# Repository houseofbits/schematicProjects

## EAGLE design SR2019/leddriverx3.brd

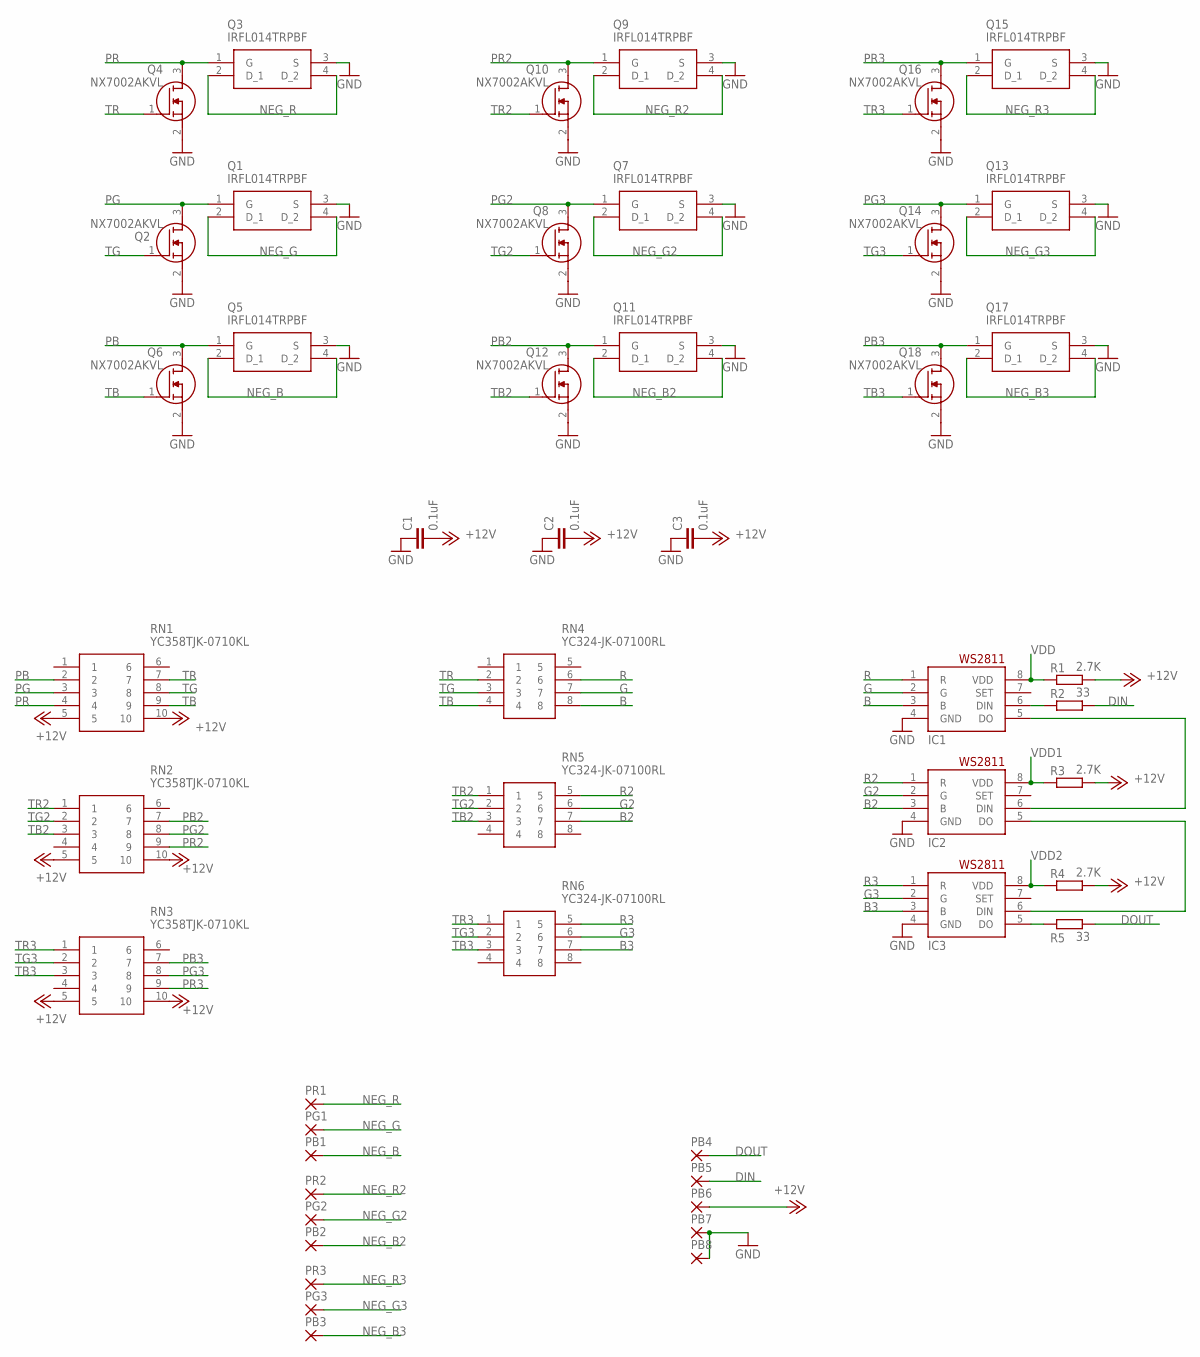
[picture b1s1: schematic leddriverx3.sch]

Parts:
C1, C2, C3: 0.1uF; C1206
IC1, IC2, IC3: WS2811-SOP8; SO08-SKINNYPADS
PB1, PB2, PB3, PB4, PB5, PB6, PB7, PB8: 3,81/1,4
PG1, PG2, PG3: 3,81/1,4
PR1, PR2, PR3: 3,81/1,4
Q1, Q3, Q5, Q7, Q9, Q11, Q13, Q15, Q17: IRFL014TRPBF; SOT230P700X180-4N
Q2, Q4, Q6, Q8, Q10, Q12, Q14, Q16, Q18: NX7002AKVL; SOT95P230X110-3N
R1, R3, R4: 2.7K; R1206
R2, R5: 33; R1206
RN1, RN2, RN3: YC358TJK-0710KL; YC358T
RN4, RN5, RN6: YC324-JK-07100RL; YC324JK07100RL

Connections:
+12V: C1.2, C2.2, C3.2, PB6.1, R1.2, R3.2, R4.2, RN1.5, RN1.10, RN2.5, RN2.10, RN3.5, RN3.10
B: IC1.3 (B), RN4.8
B2: IC2.3 (B), RN5.7
B3: IC3.3 (B), RN6.7
DIN: PB5.1, R2.2
DOUT: PB4.1, R5.2
G: IC1.2 (G), RN4.7
G2: IC2.2 (G), RN5.6
G3: IC3.2 (G), RN6.6
GND: C1.1, C2.1, C3.1, IC1.4 (GND), IC2.4 (GND), IC3.4 (GND), PB7.1, PB8.1, Q1.3 (S), Q2.2 (S), Q3.3 (S), Q4.2 (S), Q5.3 (S), Q6.2 (S), Q7.3 (S), Q8.2 (S), Q9.3 (S), Q10.2 (S), Q11.3 (S), Q12.2 (S), Q13.3 (S), Q14.2 (S), Q15.3 (S), Q16.2 (S), Q17.3 (S), Q18.2 (S)
unnamed: IC1.6 (DIN), R2.1
unnamed: IC3.5 (DO), R5.1
unnamed: IC1.5 (DO), IC2.6 (DIN)
unnamed: IC2.5 (DO), IC3.6 (DIN)
NEG_B: PB1.1, Q5.2 (D_1), Q5.4 (D_2)
NEG_B2: PB2.1, Q11.2 (D_1), Q11.4 (D_2)
NEG_B3: PB3.1, Q17.2 (D_1), Q17.4 (D_2)
NEG_G: PG1.1, Q1.2 (D_1), Q1.4 (D_2)
NEG_G2: PG2.1, Q7.2 (D_1), Q7.4 (D_2)
NEG_G3: PG3.1, Q13.2 (D_1), Q13.4 (D_2)
NEG_R: PR1.1, Q3.2 (D_1), Q3.4 (D_2)
NEG_R2: PR2.1, Q9.2 (D_1), Q9.4 (D_2)
NEG_R3: PR3.1, Q15.2 (D_1), Q15.4 (D_2)
PB: Q5.1 (G), Q6.3 (D), RN1.2
PB2: Q11.1 (G), Q12.3 (D), RN2.7
PB3: Q17.1 (G), Q18.3 (D), RN3.7
PG: Q1.1 (G), Q2.3 (D), RN1.3
PG2: Q7.1 (G), Q8.3 (D), RN2.8
PG3: Q13.1 (G), Q14.3 (D), RN3.8
PR: Q3.1 (G), Q4.3 (D), RN1.4
PR2: Q9.1 (G), Q10.3 (D), RN2.9
PR3: Q15.1 (G), Q16.3 (D), RN3.9
R: IC1.1 (R), RN4.6
R2: IC2.1 (R), RN5.5
R3: IC3.1 (R), RN6.5
TB: Q6.1 (G), RN1.9, RN4.4
TB2: Q12.1 (G), RN2.3, RN5.3
TB3: Q18.1 (G), RN3.3, RN6.3
TG: Q2.1 (G), RN1.8, RN4.3
TG2: Q8.1 (G), RN2.2, RN5.2
TG3: Q14.1 (G), RN3.2, RN6.2
TR: Q4.1 (G), RN1.7, RN4.2
TR2: Q10.1 (G), RN2.1, RN5.1
TR3: Q16.1 (G), RN3.1, RN6.1
VDD: IC1.8 (VDD), R1.1
VDD1: IC2.8 (VDD), R3.1
VDD2: IC3.8 (VDD), R4.1

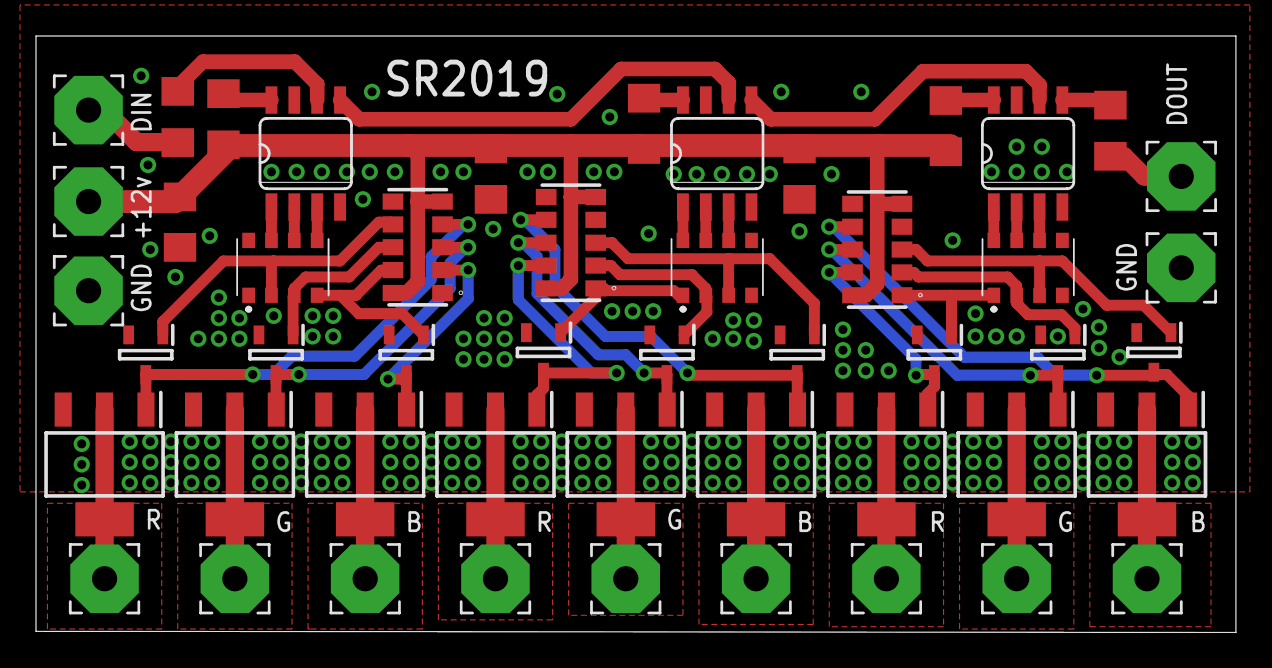
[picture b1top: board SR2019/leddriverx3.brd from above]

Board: 2 copper layers, 66.7 x 33.1 mm, 49 parts (0 on the bottom side), 47 nets.

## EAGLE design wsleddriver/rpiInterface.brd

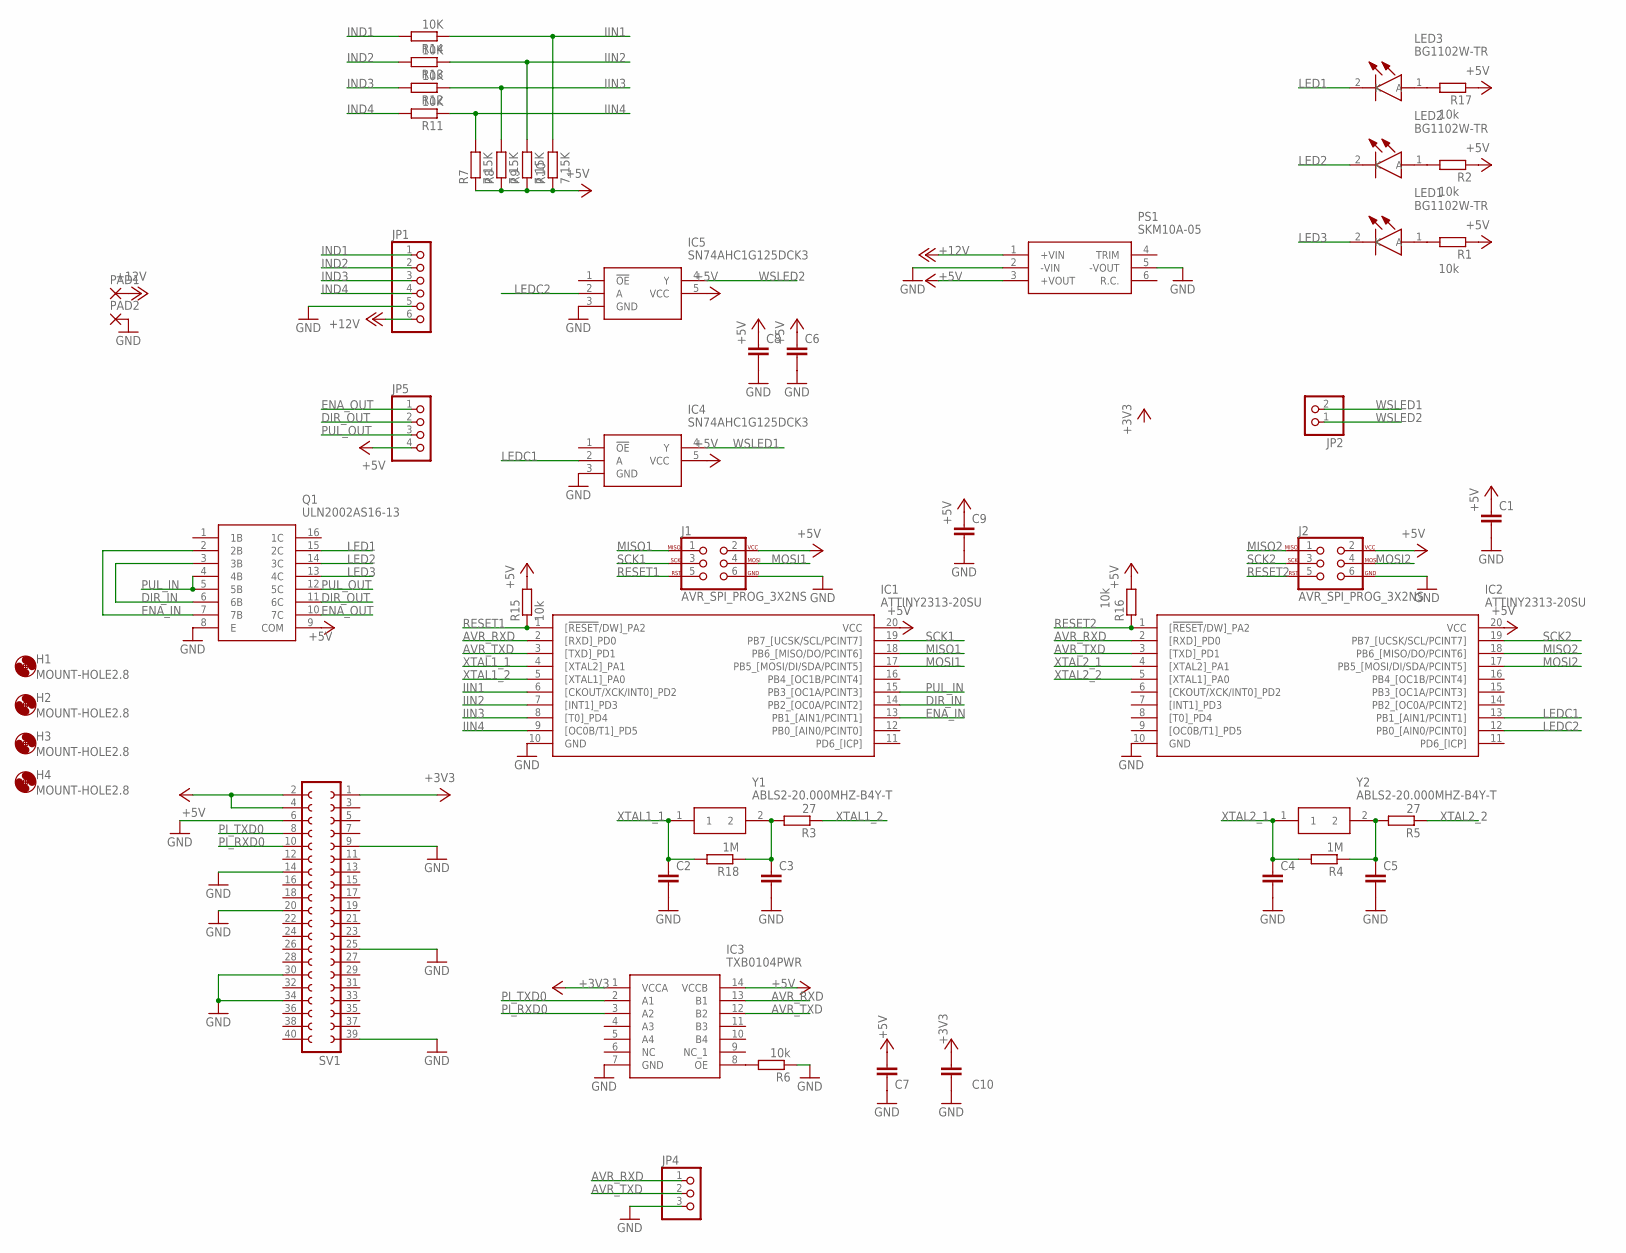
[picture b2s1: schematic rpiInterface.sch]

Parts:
C1, C2, C3, C4, C5, C6, C7, C8, C9, C10: C-EUC1206; C1206
H1, H2, H3, H4: MOUNT-HOLE2.8; 2,8
IC1, IC2: ATTINY2313-20SU; SOIC127P1032X265-20N
IC3: TXB0104PWR; SOP65P640X120-14N
IC4, IC5: SN74AHC1G125DCK3; SOT65P210X110-5N
J1, J2: AVR_SPI_PROG_3X2NS; 2X3-NS
JP1: PINHD-1X6; 1X06
JP2: PINHD-1X2; 1X02
JP4: PINHD-1X3; 1X03
JP5: PINHD-1X4; 1X04
LED1, LED2, LED3: BG1102W-TR; BG1102WTR
PAD1, PAD2: 3,17/1,3
PS1: SKM10A-05; SKM10A05
Q1: ULN2002AS16-13; SOIC127P605X126-16N
R1, R2, R6, R15, R16, R17: 10k; R1206
R3, R5: 27; R1206
R4, R18: 1M; R1206
R7, R8, R9, R10: 7.15K; R1206
R11, R12, R13, R14: 10K; R1206
SV1: FE20-2
Y1, Y2: ABLS2-20.000MHZ-B4Y-T; HC/49US-(AT49)_1

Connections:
+3V3: C10.1, IC3.1 (VCCA), SV1.1
+5V: C1.1, C6.1, C7.1, C8.1, C9.1, IC1.20 (VCC), IC2.20 (VCC), IC3.14 (VCCB), IC4.5 (VCC), IC5.5 (VCC), J1.2, J2.2, JP5.4, PS1.3 (+VOUT), Q1.9 (COM), R1.1, R2.1, R7.1, R8.1, R9.1, R10.1, R15.2, R16.2, R17.1, SV1.2, SV1.4
+12V: JP1.6, PAD1.1, PS1.1 (+VIN)
AVR_RXD: IC1.2 ([RXD]_PD0), IC2.2 ([RXD]_PD0), IC3.13 (B1), JP4.1
AVR_TXD: IC1.3 ([TXD]_PD1), IC2.3 ([TXD]_PD1), IC3.12 (B2), JP4.2
DIR_IN: IC1.14 (PB2_[OC0A/PCINT2]), Q1.3 (3B), Q1.6 (6B)
DIR_OUT: JP5.2, Q1.11 (6C)
ENA_IN: IC1.13 (PB1_[AIN1/PCINT1]), Q1.2 (2B), Q1.7 (7B)
ENA_OUT: JP5.1, Q1.10 (7C)
GND: C1.2, C2.2, C3.2, C4.2, C5.2, C6.2, C7.2, C8.2, C9.2, C10.2, IC1.10 (GND), IC2.10 (GND), IC3.7 (GND), IC4.3 (GND), IC5.3 (GND), J1.6, J2.6, JP1.5, JP4.3, PAD2.1, PS1.2 (-VIN), PS1.5 (-VOUT), Q1.8 (E), R6.1, SV1.6, SV1.9, SV1.14, SV1.20, SV1.25, SV1.30, SV1.34, SV1.39
IIN1: IC1.6 ([CKOUT/XCK/INT0]_PD2), R10.2, R14.1
IIN2: IC1.7 ([INT1]_PD3), R9.2, R13.1
IIN3: IC1.8 ([T0]_PD4), R8.2, R12.1
IIN4: IC1.9 ([OC0B/T1]_PD5), R7.2, R11.1
IND1: JP1.1, R14.2
IND2: JP1.2, R13.2
IND3: JP1.3, R12.2
IND4: JP1.4, R11.2
LED1: LED3.2 (K), Q1.15 (2C)
LED2: LED2.2 (K), Q1.14 (3C)
LED3: LED1.2 (K), Q1.13 (4C)
LEDC1: IC2.13 (PB1_[AIN1/PCINT1]), IC4.2 (A)
LEDC2: IC2.12 (PB0_[AIN0/PCINT0]), IC5.2 (A)
MISO1: IC1.18 (PB6_[MISO/DO/PCINT6]), J1.1
MISO2: IC2.18 (PB6_[MISO/DO/PCINT6]), J2.1
MOSI1: IC1.17 (PB5_[MOSI/DI/SDA/PCINT5]), J1.4
MOSI2: IC2.17 (PB5_[MOSI/DI/SDA/PCINT5]), J2.4
unnamed: C3.1, R3.2, R18.1, Y1.2
unnamed: C5.1, R4.1, R5.2, Y2.2
unnamed: LED1.1 (A), R1.2
unnamed: LED2.1 (A), R2.2
unnamed: LED3.1 (A), R17.2
unnamed: IC3.8 (OE), R6.2
PI_RXD0: IC3.3 (A2), SV1.10
PI_TXD0: IC3.2 (A1), SV1.8
PUL_IN: IC1.15 (PB3_[OC1A/PCINT3]), Q1.4 (4B), Q1.5 (5B)
PUL_OUT: JP5.3, Q1.12 (5C)
RESET1: IC1.1 ([!RESET!/DW]_PA2), J1.5, R15.1
RESET2: IC2.1 ([!RESET!/DW]_PA2), J2.5, R16.1
SCK1: IC1.19 (PB7_[UCSK/SCL/PCINT7]), J1.3
SCK2: IC2.19 (PB7_[UCSK/SCL/PCINT7]), J2.3
WSLED1: IC4.4 (Y), JP2.2
WSLED2: IC5.4 (Y), JP2.1
XTAL1_1: C2.1, IC1.4 ([XTAL2]_PA1), R18.2, Y1.1
XTAL1_2: IC1.5 ([XTAL1]_PA0), R3.1
XTAL2_1: C4.1, IC2.4 ([XTAL2]_PA1), R4.2, Y2.1
XTAL2_2: IC2.5 ([XTAL1]_PA0), R5.1

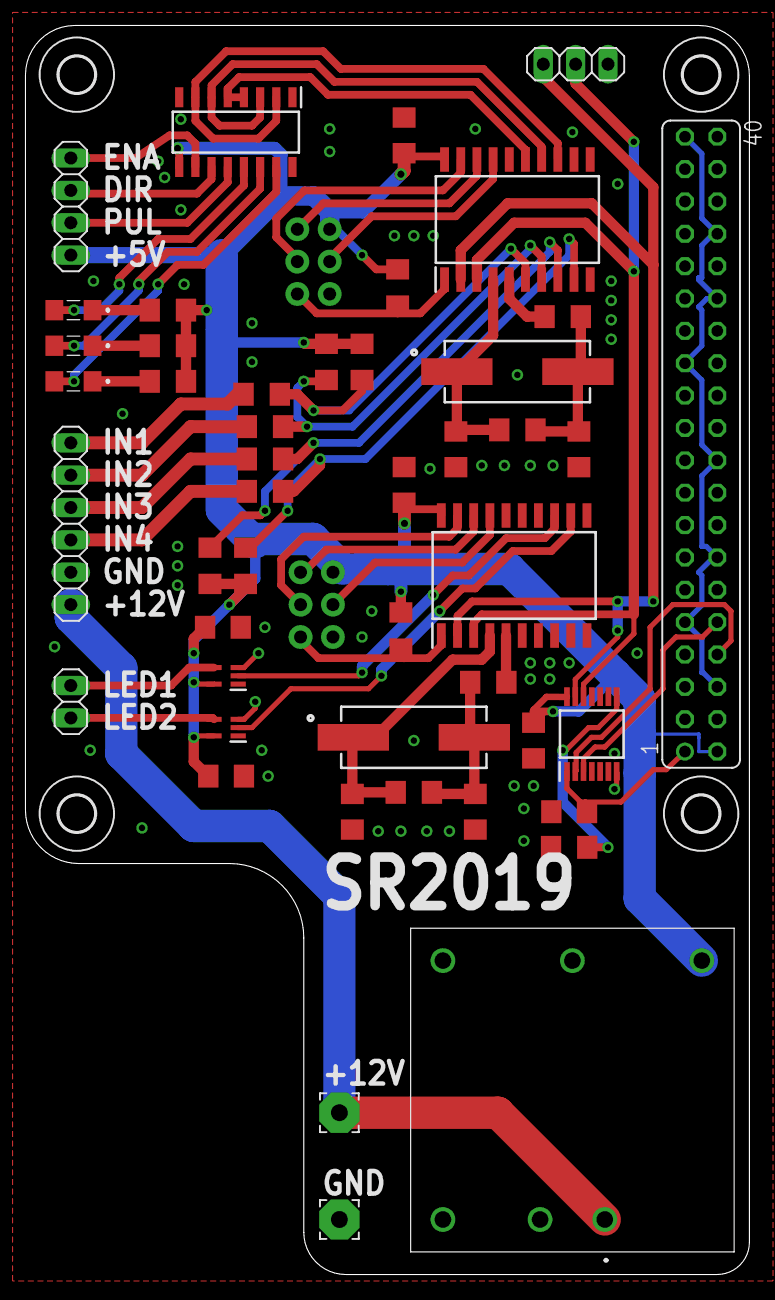
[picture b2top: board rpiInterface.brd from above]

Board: 2 copper layers, 56.8 x 98.0 mm, 53 parts (0 on the bottom side), 47 nets.

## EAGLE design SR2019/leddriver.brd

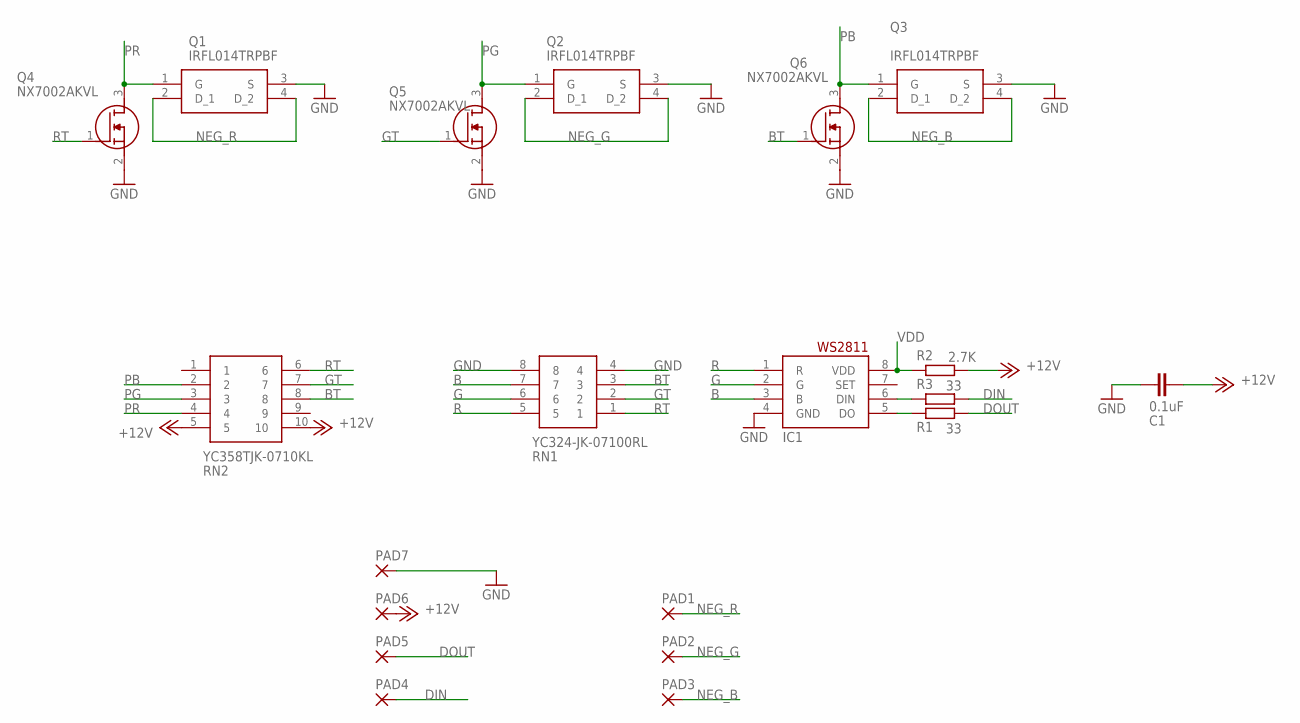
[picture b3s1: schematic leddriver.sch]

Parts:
C1: 0.1uF; C1206
IC1: WS2811-SOP8; SO08-SKINNYPADS
PAD1, PAD2, PAD3, PAD4, PAD5, PAD6, PAD7: 3,81/1,4
Q1, Q2, Q3: IRFL014TRPBF; SOT230P700X180-4N
Q4, Q5, Q6: NX7002AKVL; SOT95P230X110-3N
R1, R3: 33; R1206
R2: 2.7K; R1206
RN1: YC324-JK-07100RL; YC324JK07100RL
RN2: YC358TJK-0710KL; YC358T

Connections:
+12V: C1.2, PAD6.1, R2.1, RN2.5, RN2.10
B: IC1.3 (B), RN1.7
BT: Q6.1 (G), RN1.3, RN2.8
DIN: PAD4.1, R3.1
DOUT: PAD5.1, R1.1
G: IC1.2 (G), RN1.6
GND: C1.1, IC1.4 (GND), PAD7.1, Q1.3 (S), Q2.3 (S), Q3.3 (S), Q4.2 (S), Q5.2 (S), Q6.2 (S), RN1.4, RN1.8
GT: Q5.1 (G), RN1.2, RN2.7
unnamed: IC1.6 (DIN), R3.2
unnamed: IC1.5 (DO), R1.2
NEG_B: PAD3.1, Q3.2 (D_1), Q3.4 (D_2)
NEG_G: PAD2.1, Q2.2 (D_1), Q2.4 (D_2)
NEG_R: PAD1.1, Q1.2 (D_1), Q1.4 (D_2)
PB: Q3.1 (G), Q6.3 (D), RN2.2
PG: Q2.1 (G), Q5.3 (D), RN2.3
PR: Q1.1 (G), Q4.3 (D), RN2.4
R: IC1.1 (R), RN1.5
RT: Q4.1 (G), RN1.1, RN2.6
VDD: IC1.8 (VDD), R2.2

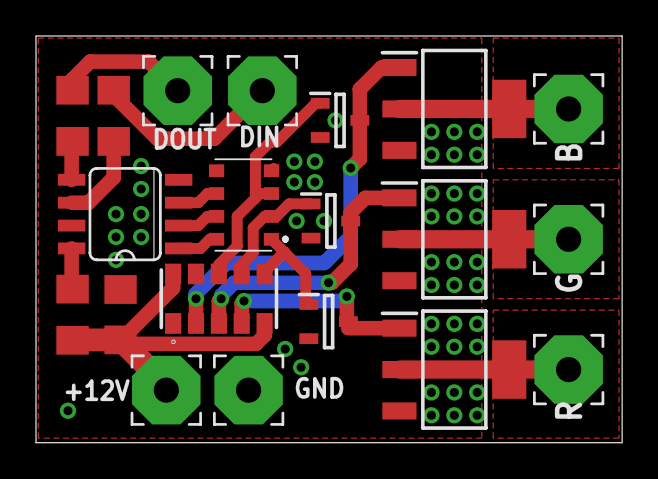
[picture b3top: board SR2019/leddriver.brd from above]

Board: 2 copper layers, 32.6 x 22.6 mm, 20 parts (0 on the bottom side), 19 nets.

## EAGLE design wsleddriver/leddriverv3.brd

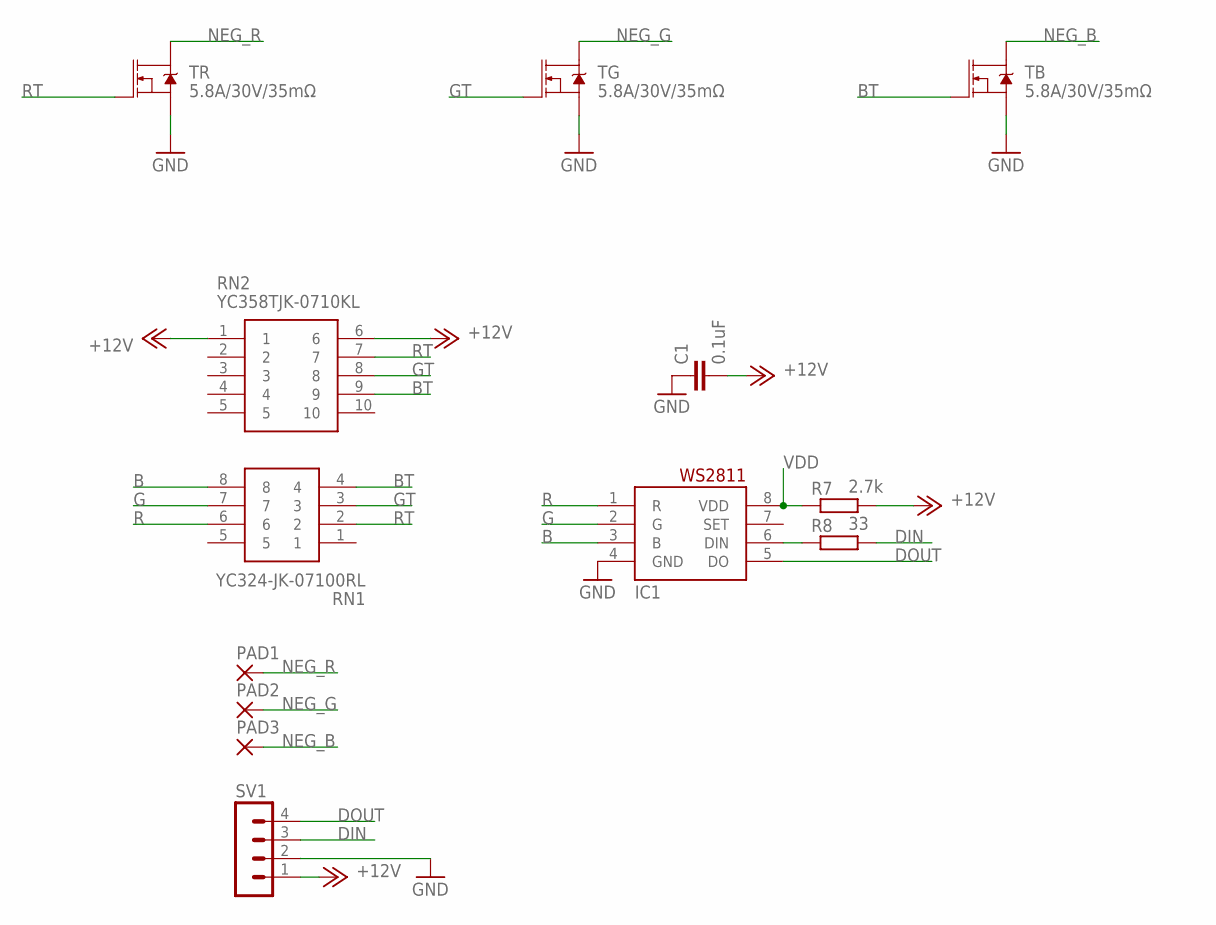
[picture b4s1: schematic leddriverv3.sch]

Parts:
C1: 0.1uF; C1206
IC1: WS2811-SOP8; SO08-SKINNYPADS
PAD1, PAD2, PAD3: 3,81/1,4
R7: 2.7k; R0805
R8: 33; R0805
RN1: YC324-JK-07100RL; YC324JK07100RL
RN2: YC358TJK-0710KL; YC358T
SV1: MA04-1
TB: 5.8A/30V/35mΩ; SOT23-3
TG: 5.8A/30V/35mΩ; SOT23-3
TR: 5.8A/30V/35mΩ; SOT23-3

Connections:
+12V: C1.2, R7.2, RN2.1, RN2.6, SV1.1
B: IC1.3 (B), RN1.8
BT: RN1.4, RN2.9, TB.1 (G)
DIN: R8.2, SV1.3
DOUT: IC1.5 (DO), SV1.4
G: IC1.2 (G), RN1.7
GND: C1.1, IC1.4 (GND), SV1.2, TB.2 (S), TG.2 (S), TR.2 (S)
GT: RN1.3, RN2.8, TG.1 (G)
unnamed: IC1.6 (DIN), R8.1
NEG_B: PAD3.1, TB.3 (D)
NEG_G: PAD2.1, TG.3 (D)
NEG_R: PAD1.1, TR.3 (D)
R: IC1.1 (R), RN1.6
RT: RN1.2, RN2.7, TR.1 (G)
VDD: IC1.8 (VDD), R7.1

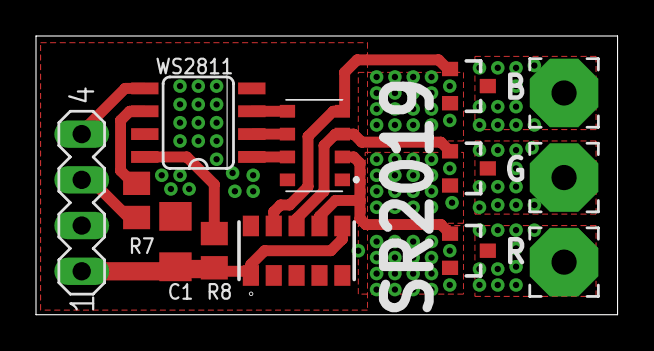
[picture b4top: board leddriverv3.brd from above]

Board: 2 copper layers, 32.3 x 15.5 mm, 13 parts (0 on the bottom side), 15 nets.

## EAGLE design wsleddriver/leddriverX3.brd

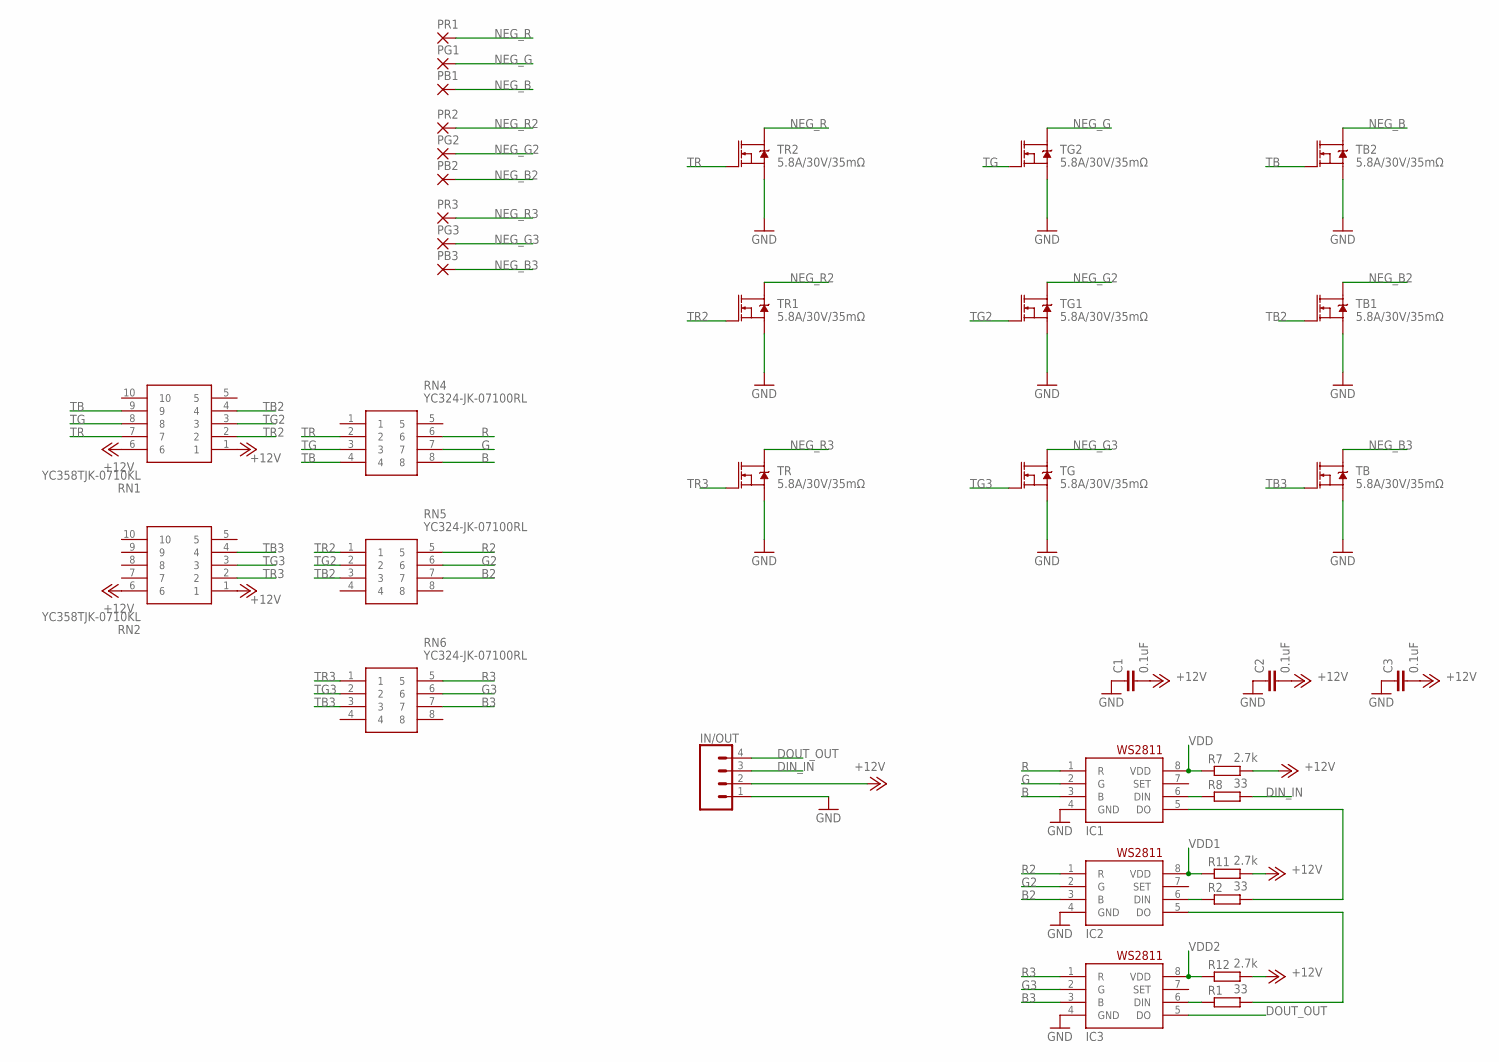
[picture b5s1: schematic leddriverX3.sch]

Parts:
C1, C2, C3: 0.1uF; C1206
IC1, IC2, IC3: WS2811-SOP8; SO08-SKINNYPADS
IN/OUT: CONN_04LONGPADS; 1X04_LONGPADS
PB1, PB2, PB3: 3,81/1,4
PG1, PG2, PG3: 3,81/1,4
PR1, PR2, PR3: 3,81/1,4
R1, R2, R8: 33; R0805
R7, R11, R12: 2.7k; R0805
RN1, RN2: YC358TJK-0710KL; YC358T
RN4, RN5, RN6: YC324-JK-07100RL; YC324JK07100RL
TB, TB1, TB2: 5.8A/30V/35mΩ; SOT23-3
TG, TG1, TG2: 5.8A/30V/35mΩ; SOT23-3
TR, TR1, TR2: 5.8A/30V/35mΩ; SOT23-3

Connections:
+12V: C1.2, C2.2, C3.2, IN/OUT.2, R7.2, R11.2, R12.2, RN1.1, RN1.6, RN2.1, RN2.6
B: IC1.3 (B), RN4.8
B2: IC2.3 (B), RN5.7
B3: IC3.3 (B), RN6.7
DIN_IN: IN/OUT.3, R8.2
DOUT_OUT: IC3.5 (DO), IN/OUT.4
G: IC1.2 (G), RN4.7
G2: IC2.2 (G), RN5.6
G3: IC3.2 (G), RN6.6
GND: C1.1, C2.1, C3.1, IC1.4 (GND), IC2.4 (GND), IC3.4 (GND), IN/OUT.1, TB.2 (S), TB1.2 (S), TB2.2 (S), TG.2 (S), TG1.2 (S), TG2.2 (S), TR.2 (S), TR1.2 (S), TR2.2 (S)
unnamed: IC1.6 (DIN), R8.1
unnamed: IC1.5 (DO), R2.2
unnamed: IC2.5 (DO), R1.2
unnamed: IC3.6 (DIN), R1.1
unnamed: IC2.6 (DIN), R2.1
NEG_B: PB1.1, TB2.3 (D)
NEG_B2: PB2.1, TB1.3 (D)
NEG_B3: PB3.1, TB.3 (D)
NEG_G: PG1.1, TG2.3 (D)
NEG_G2: PG2.1, TG1.3 (D)
NEG_G3: PG3.1, TG.3 (D)
NEG_R: PR1.1, TR2.3 (D)
NEG_R2: PR2.1, TR1.3 (D)
NEG_R3: PR3.1, TR.3 (D)
R: IC1.1 (R), RN4.6
R2: IC2.1 (R), RN5.5
R3: IC3.1 (R), RN6.5
TB: RN1.9, RN4.4, TB2.1 (G)
TB2: RN1.4, RN5.3, TB1.1 (G)
TB3: RN2.4, RN6.3, TB.1 (G)
TG: RN1.8, RN4.3, TG2.1 (G)
TG2: RN1.3, RN5.2, TG1.1 (G)
TG3: RN2.3, RN6.2, TG.1 (G)
TR: RN1.7, RN4.2, TR2.1 (G)
TR2: RN1.2, RN5.1, TR1.1 (G)
TR3: RN2.2, RN6.1, TR.1 (G)
VDD: IC1.8 (VDD), R7.1
VDD1: IC2.8 (VDD), R11.1
VDD2: IC3.8 (VDD), R12.1

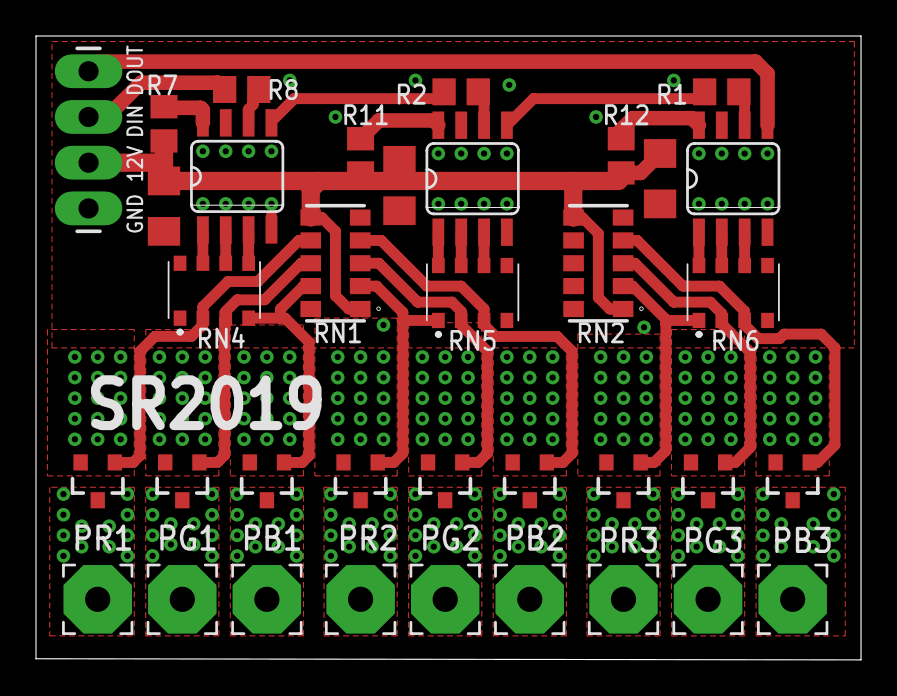
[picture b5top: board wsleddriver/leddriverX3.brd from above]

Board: 2 copper layers, 45.8 x 34.7 mm, 36 parts (0 on the bottom side), 39 nets.

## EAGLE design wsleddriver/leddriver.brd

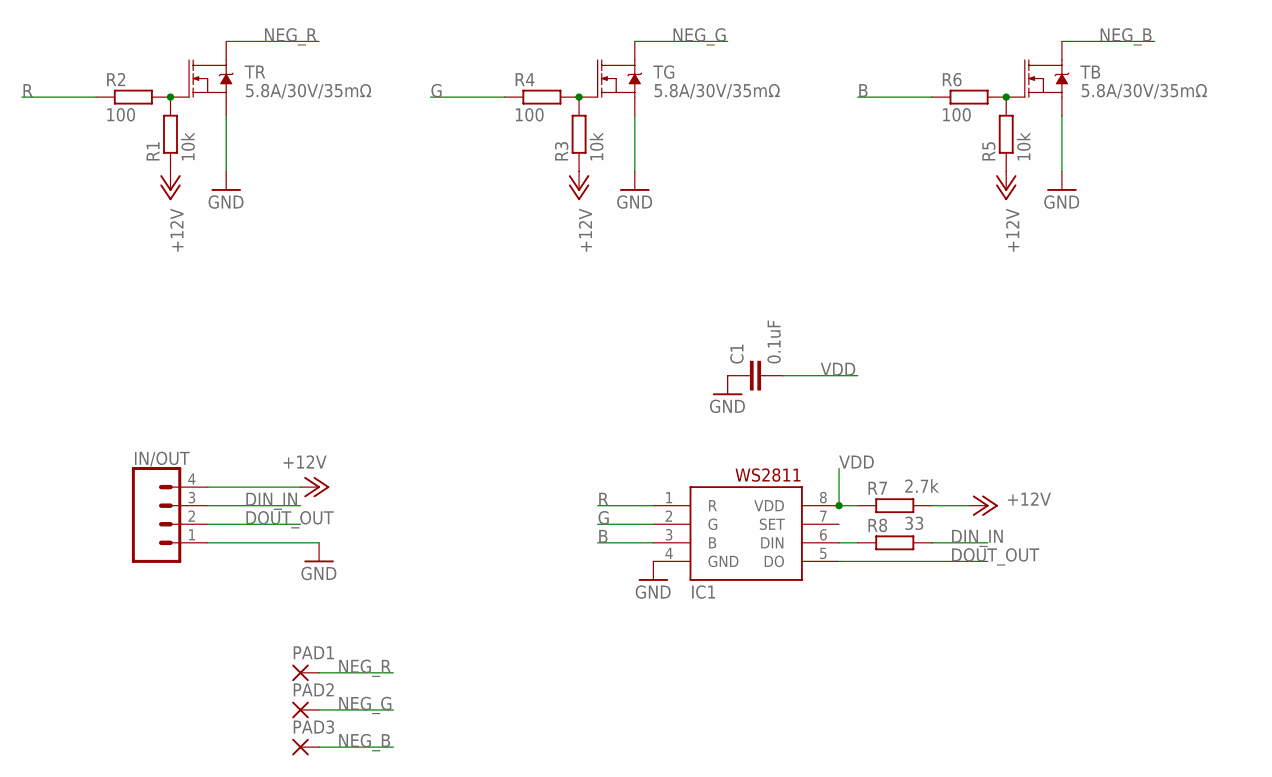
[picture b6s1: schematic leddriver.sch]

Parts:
C1: 0.1uF; C1206
IC1: WS2811-SOP8; SO08-SKINNYPADS
IN/OUT: CONN_04LONGPADS; 1X04_LONGPADS
PAD1, PAD2, PAD3: 3,81/1,4
R1, R3, R5: 10k; R0805
R2, R4, R6: 100; R0805
R7: 2.7k; R0805
R8: 33; R0805
TB: 5.8A/30V/35mΩ; SOT23-3
TG: 5.8A/30V/35mΩ; SOT23-3
TR: 5.8A/30V/35mΩ; SOT23-3

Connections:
+12V: IN/OUT.4, R1.1, R3.1, R5.1, R7.2
B: IC1.3 (B), R6.1
DIN_IN: IN/OUT.3, R8.2
DOUT_OUT: IC1.5 (DO), IN/OUT.2
G: IC1.2 (G), R4.1
GND: C1.1, IC1.4 (GND), IN/OUT.1, TB.2 (S), TG.2 (S), TR.2 (S)
unnamed: IC1.6 (DIN), R8.1
unnamed: R3.2, R4.2, TG.1 (G)
unnamed: R5.2, R6.2, TB.1 (G)
unnamed: R1.2, R2.2, TR.1 (G)
NEG_B: PAD3.1, TB.3 (D)
NEG_G: PAD2.1, TG.3 (D)
NEG_R: PAD1.1, TR.3 (D)
R: IC1.1 (R), R2.1
VDD: C1.2, IC1.8 (VDD), R7.1

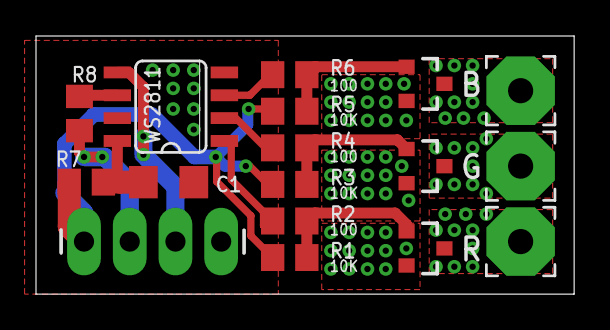
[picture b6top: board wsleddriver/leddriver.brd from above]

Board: 2 copper layers, 29.9 x 14.3 mm, 17 parts (0 on the bottom side), 15 nets.

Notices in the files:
parts and their libraries:
SparkFun-AnalogIC: Licensing:Creative Commons ShareAlike 4.0 International - https://creativecommons.org/licenses/by-sa/4.0
